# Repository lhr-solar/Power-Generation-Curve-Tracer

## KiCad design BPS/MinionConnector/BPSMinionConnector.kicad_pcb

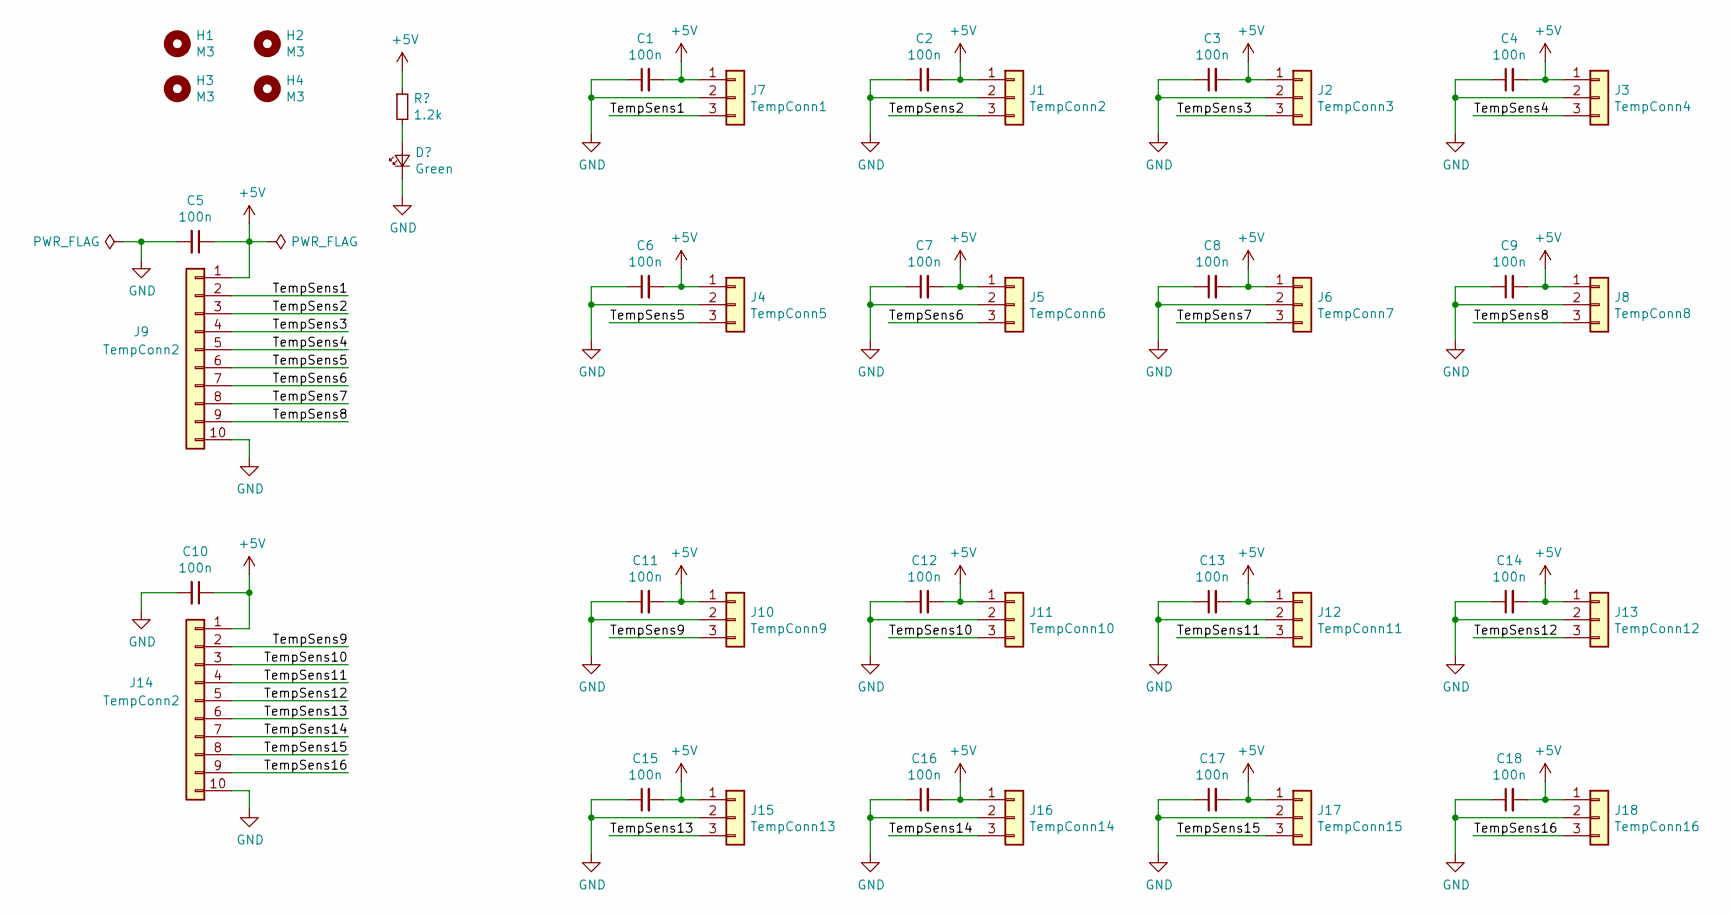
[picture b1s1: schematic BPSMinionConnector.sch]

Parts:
C1, C2, C3, C4, C5, C6, C7, C8, C9, C10, C11, C12, C13, C14, C15, C16, C17, C18: 100n; C_0805_2012Metric
H1, H2, H3, H4: M3; MountingHole_3mm
J1: TempConn2; Molex_Micro-Fit_3.0_43650-0315_1x03_P3.00mm_Vertical
J2: TempConn3; Molex_Micro-Fit_3.0_43650-0315_1x03_P3.00mm_Vertical
J3: TempConn4; Molex_Micro-Fit_3.0_43650-0315_1x03_P3.00mm_Vertical
J4: TempConn5; Molex_Micro-Fit_3.0_43650-0315_1x03_P3.00mm_Vertical
J5: TempConn6; Molex_Micro-Fit_3.0_43650-0315_1x03_P3.00mm_Vertical
J6: TempConn7; Molex_Micro-Fit_3.0_43650-0315_1x03_P3.00mm_Vertical
J7: TempConn1; Molex_Micro-Fit_3.0_43650-0315_1x03_P3.00mm_Vertical
J8: TempConn8; Molex_Micro-Fit_3.0_43650-0315_1x03_P3.00mm_Vertical
J9, J14: TempConn2; PinHeader_1x10_P2.54mm_Vertical
J10: TempConn9; Molex_Micro-Fit_3.0_43650-0315_1x03_P3.00mm_Vertical
J11: TempConn10; Molex_Micro-Fit_3.0_43650-0315_1x03_P3.00mm_Vertical
J12: TempConn11; Molex_Micro-Fit_3.0_43650-0315_1x03_P3.00mm_Vertical
J13: TempConn12; Molex_Micro-Fit_3.0_43650-0315_1x03_P3.00mm_Vertical
J15: TempConn13; Molex_Micro-Fit_3.0_43650-0315_1x03_P3.00mm_Vertical
J16: TempConn14; Molex_Micro-Fit_3.0_43650-0315_1x03_P3.00mm_Vertical
J17: TempConn15; Molex_Micro-Fit_3.0_43650-0315_1x03_P3.00mm_Vertical
J18: TempConn16; Molex_Micro-Fit_3.0_43650-0315_1x03_P3.00mm_Vertical

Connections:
+5V: C1.2, C2.2, C3.2, C4.2, C5.1, C6.2, C7.2, C8.2, C9.2, C10.1, C11.2, C12.2, C13.2, C14.2, C15.2, C16.2, C17.2, C18.2, J1.1, J2.1, J3.1, J4.1, J5.1, J6.1, J7.1, J8.1, J9.1, J10.1, J11.1, J12.1, J13.1, J14.1, J15.1, J16.1, J17.1, J18.1; also elsewhere on the board
/TempSens1: J7.3, J9.2
/TempSens2: J1.3, J9.3
/TempSens3: J2.3, J9.4
/TempSens4: J3.3, J9.5
/TempSens5: J4.3, J9.6
/TempSens6: J5.3, J9.7
/TempSens7: J6.3, J9.8
/TempSens8: J8.3, J9.9
/TempSens9: J10.3, J14.2
/TempSens10: J11.3, J14.3
/TempSens11: J12.3, J14.4
/TempSens12: J13.3, J14.5
/TempSens13: J14.6, J15.3
/TempSens14: J14.7, J16.3
/TempSens15: J14.8, J17.3
/TempSens16: J14.9, J18.3
GND: C1.1, C2.1, C3.1, C4.1, C5.2, C6.1, C7.1, C8.1, C9.1, C10.2, C11.1, C12.1, C13.1, C14.1, C15.1, C16.1, C17.1, C18.1, J1.2, J2.2, J3.2, J4.2, J5.2, J6.2, J7.2, J8.2, J9.10, J10.2, J11.2, J12.2, J13.2, J14.10, J15.2, J16.2, J17.2, J18.2; also elsewhere on the board

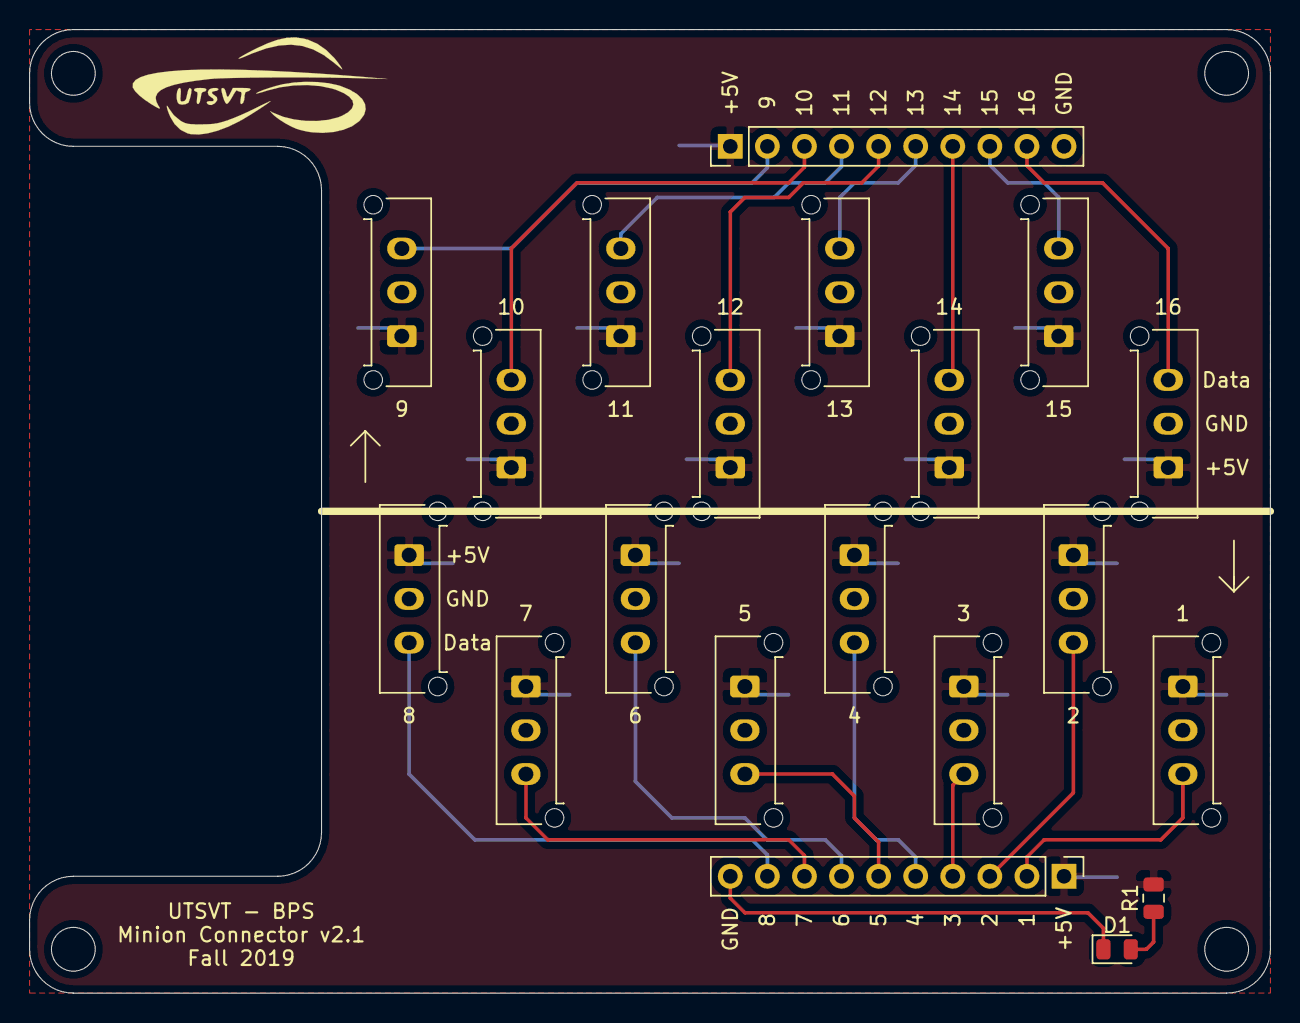
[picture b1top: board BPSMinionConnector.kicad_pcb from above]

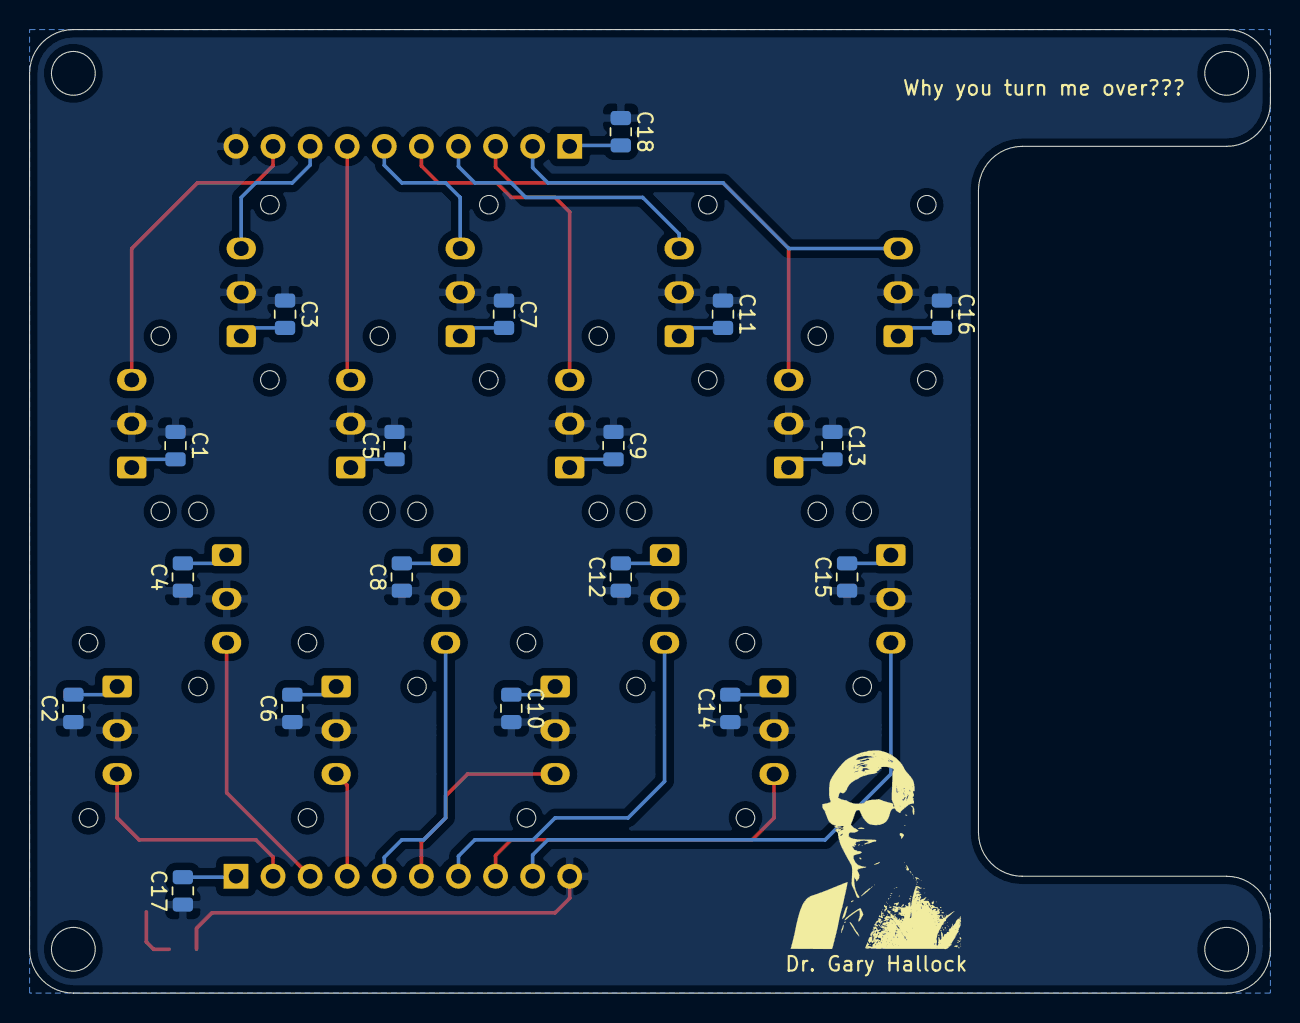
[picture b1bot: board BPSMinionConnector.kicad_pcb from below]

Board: 2 copper layers, 85.0 x 66.0 mm, 42 parts (18 on the bottom side), 19 nets.

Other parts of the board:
D1: Green; LED_0805_2012Metric
R1: 1.2k; R_0805_2012Metric

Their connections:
+5V: R1.1; also elsewhere on the board
GND: D1.1; also elsewhere on the board
unnamed: D1.2, R1.2

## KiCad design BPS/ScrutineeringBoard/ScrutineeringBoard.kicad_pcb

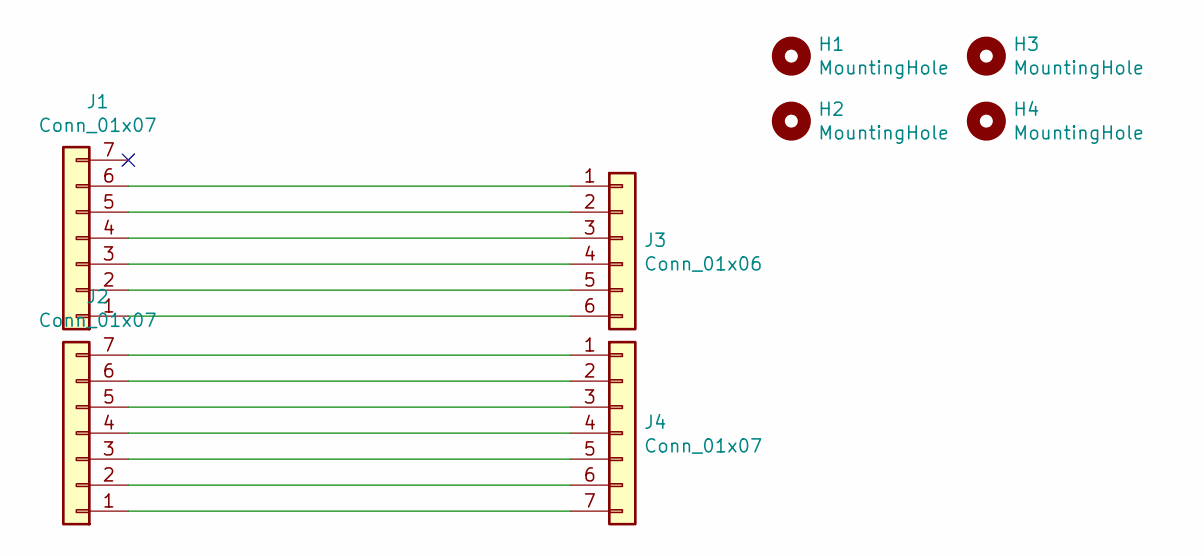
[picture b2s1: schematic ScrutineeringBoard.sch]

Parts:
H1, H2, H3, H4: MountingHole; MountingHole_3mm
J1, J2: Conn_01x07; Molex_Micro-Fit_3.0_43650-0700_1x07_P3.00mm_Horizontal
J3: Conn_01x06; PinHeader_1x06_P2.54mm_Horizontal
J4: Conn_01x07; PinHeader_1x07_P2.54mm_Horizontal

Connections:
unnamed: J1.1, J3.6
unnamed: J1.2, J3.5
unnamed: J1.3, J3.4
unnamed: J1.4, J3.3
unnamed: J1.5, J3.2
unnamed: J1.6, J3.1
unnamed: J2.1, J4.7
unnamed: J2.2, J4.6
unnamed: J2.3, J4.5
unnamed: J2.4, J4.4
unnamed: J2.5, J4.3
unnamed: J2.6, J4.2
unnamed: J2.7, J4.1

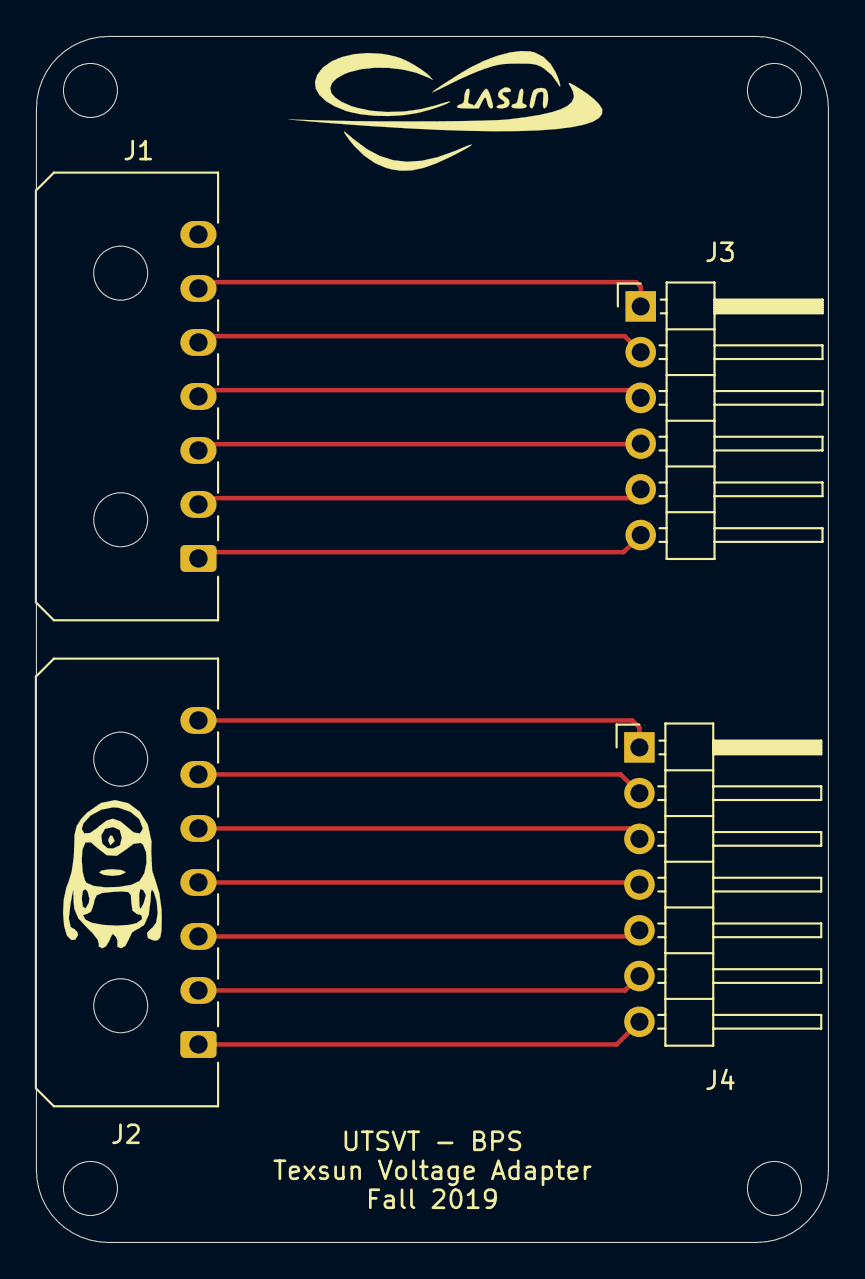
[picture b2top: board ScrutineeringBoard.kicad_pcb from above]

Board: 2 copper layers, 44.0 x 67.0 mm, 8 parts (0 on the bottom side), 13 nets.

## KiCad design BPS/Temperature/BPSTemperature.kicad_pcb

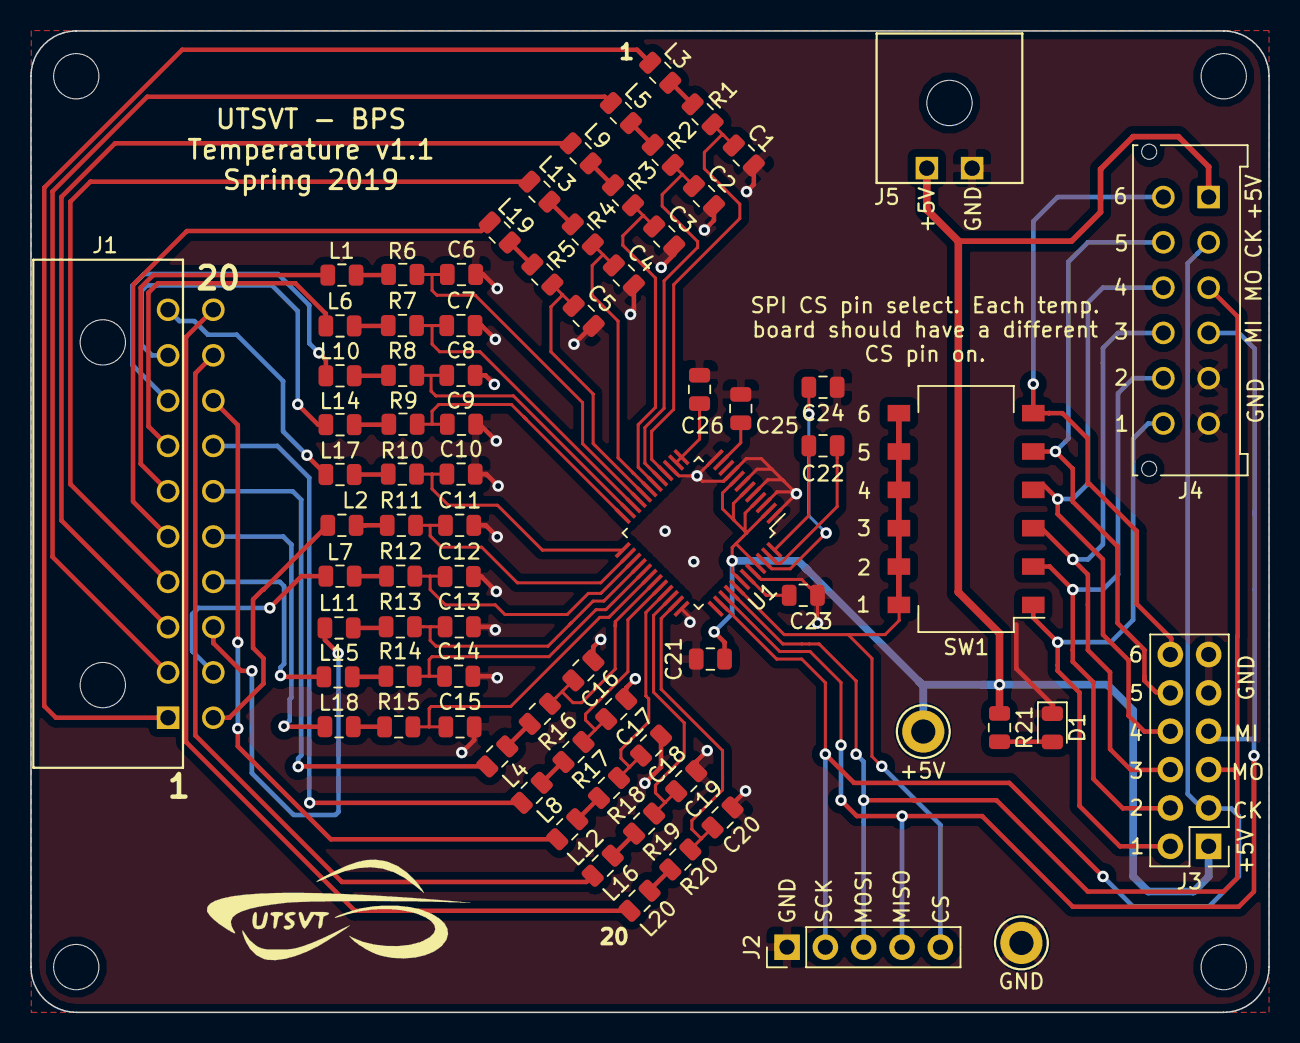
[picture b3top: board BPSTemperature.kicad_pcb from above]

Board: 2 copper layers, 82.0 x 65.0 mm, 81 parts (0 on the bottom side), 79 nets.

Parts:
C1, C2, C3, C4, C5, C6, C7, C8, C9, C10, C11, C12, C13, C14, C15, C16, C17, C18, C19, C20, C21: 0.1uF; C_0805_2012Metric
C22, C23, C24: 10uF; C_0805_2012Metric
C25, C26: 1uF; C_0805_2012Metric
D1: LED; LED_0805_2012Metric
J1: Conn_02x10_Counter_Clockwise; 02x10_Microfit_3.0_horizontal
J2: Logic Analyzer; PinHeader_1x05_P2.54mm_Vertical
J3: Conn_02x06_Counter_Clockwise; PinHeader_2x06_P2.54mm_Vertical
J4: Conn_02x06_Counter_Clockwise; Molex_MicroFit3.0_2x6xP3.00mm_PolarizingPeg_Vertical
J5: Conn_01x02; 43650-0202_01x02_Microfit 3.0_horizontal
L1, L2, L3, L4, L5, L6, L7, L8, L9, L10, L11, L12, L13, L14, L15, L16, L17, L18, L19, L20: Ferrite_Bead; L_0805_2012Metric
MH1, MH2, MH3, MH4: MountingHole; MountingHole_3mm
R1, R2, R3, R4, R5, R6, R7, R8, R9, R10, R11, R12, R13, R14, R15, R16, R17, R18, R19, R20: 1.5k; R_0805_2012Metric
R21: 1.55k; R_0805_2012Metric
SW1: SW_DIP_x06; SW_DIP_SPSTx06_Slide_Omron_A6S-610x_W8.9mm_P2.54mm
TP1, TP2: TestPoint; TestPoint_Keystone_5005-5009_Compact
U1: LTC2983; LQFP-48_7x7mm_P0.5mm

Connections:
+5V: C21.2, J3.1, J4.1, J5.1, R21.1, TP1.1, U1.2, U1.4, U1.6, U1.8, U1.42, U1.45
/CH1_LPF: J1.1, L3.2
/CH2_LPF: J1.2, L5.2
/CH3_LPF: J1.3, L9.2
/CH4_LPF: J1.4, L13.2
/CH5_LPF: J1.5, L19.2
/CH6_LPF: J1.6, L1.1
/CH7_LPF: J1.7, L6.1
/CH8_LPF: J1.8, L10.1
/CH9_LPF: J1.9, L14.1
/CH10_LPF: J1.10, L17.2
/CH11_LPF: J1.11, L2.1
/CH12_LPF: J1.12, L7.1
/CH13_LPF: J1.13, L11.1
/CH14_LPF: J1.14, L15.1
/CH15_LPF: J1.15, L18.1
/CH16_LPF: J1.16, L4.1
/CH17_LPF: J1.17, L8.1
/CH18_LPF: J1.18, L12.1
/CH19_LPF: J1.19, L16.1
/CH20_LPF: J1.20, L20.1
/CS1: J3.2, J4.12, SW1.1
/CS1_OUT: J2.5, SW1.7, SW1.8, SW1.9, SW1.10, SW1.11, SW1.12, U1.41
/CS2: J3.4, J4.11, SW1.2
/CS3: J3.6, J4.10, SW1.3
/CS4: J3.8, J4.9, SW1.4
/CS5: J3.10, J4.8, SW1.5
/CS6: J3.12, J4.7, SW1.6
/MISO: J2.4, J3.7, J4.4, U1.39
/MOSI: J2.3, J3.5, J4.3, U1.40
/SCK: J2.2, J3.3, J4.2, U1.38
GND: C1.2, C2.2, C3.2, C4.2, C5.2, C6.2, C7.2, C8.2, C9.2, C10.2, C11.2, C12.2, C13.2, C14.2, C15.2, C16.2, C17.2, C18.2, C19.2, C20.2, C21.1, C23.2, C24.2, C25.2, C26.2, D1.1, J2.1, J3.9, J3.11, J4.5, J4.6, J5.2, TP2.1, U1.1, U1.3, U1.5, U1.7, U1.9, U1.12, U1.15, U1.36, U1.44
unnamed: C1.1, R1.2, U1.16
unnamed: C2.1, R2.2, U1.17
unnamed: C3.1, R3.2, U1.18
unnamed: C4.1, R4.2, U1.19
unnamed: C5.1, R5.2, U1.20
unnamed: C6.1, R6.2, U1.21
unnamed: C7.1, R7.2, U1.22
unnamed: C8.1, R8.2, U1.23
unnamed: C9.1, R9.2, U1.24
unnamed: C10.1, R10.2, U1.25
unnamed: C11.1, R11.2, U1.26
unnamed: C12.1, R12.2, U1.27
unnamed: C13.1, R13.2, U1.28
unnamed: C14.1, R14.2, U1.29
unnamed: C15.1, R15.2, U1.30
unnamed: C16.1, R16.2, U1.31
unnamed: C17.1, R17.2, U1.32
unnamed: C18.1, R18.2, U1.33
unnamed: C19.1, R19.2, U1.34
unnamed: C20.1, R20.2, U1.35
unnamed: C22.1, U1.48
unnamed: C22.2, U1.47
unnamed: C23.1, U1.43
unnamed: C24.1, U1.46
unnamed: C25.1, U1.11
unnamed: C26.1, U1.13, U1.14
unnamed: D1.2, R21.2
unnamed: L1.2, R6.1
unnamed: L2.2, R11.1
unnamed: L3.1, R1.1
unnamed: L4.2, R16.1
unnamed: L5.1, R2.1
unnamed: L6.2, R7.1
unnamed: L7.2, R12.1
unnamed: L8.2, R17.1
unnamed: L9.1, R3.1
unnamed: L10.2, R8.1
unnamed: L11.2, R13.1
unnamed: L12.2, R18.1
unnamed: L13.1, R4.1
unnamed: L14.2, R9.1
unnamed: L15.2, R14.1
unnamed: L16.2, R19.1
unnamed: L17.1, R10.1
unnamed: L18.2, R15.1
unnamed: L19.1, R5.1
unnamed: L20.2, R20.1

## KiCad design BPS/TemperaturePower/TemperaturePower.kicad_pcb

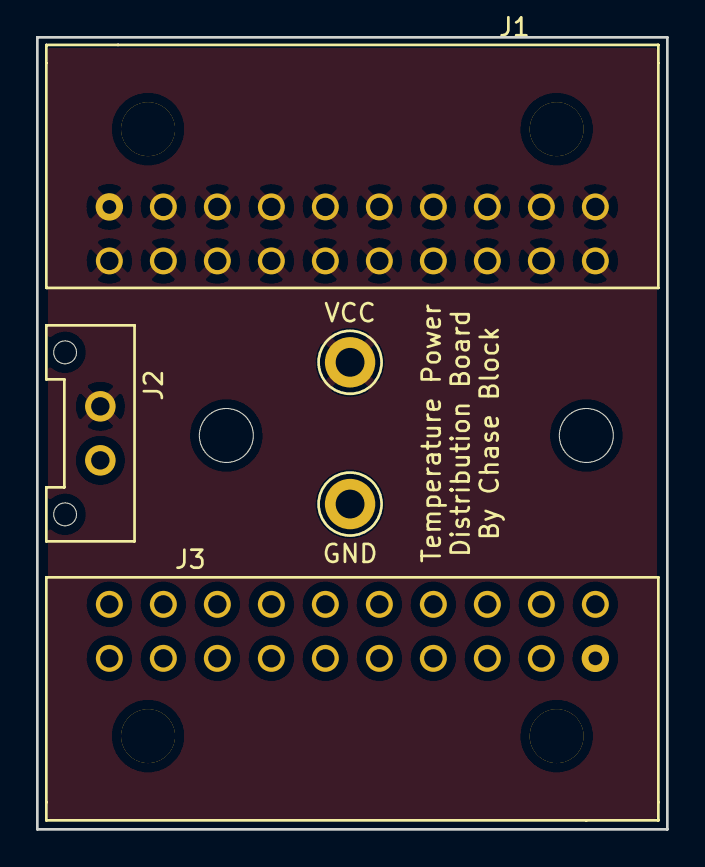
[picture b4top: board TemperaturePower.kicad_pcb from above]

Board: 2 copper layers, 35.0 x 44.0 mm, 7 parts (0 on the bottom side), 2 nets, no tracks yet.

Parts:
GND: TestPoint; TestPoint_Keystone_5005-5009_Compact
J1, J3: Conn_02x10_Counter_Clockwise; Molex2x10_horizontal
J2: Conn_01x02; Molex_MicroFit3.0_1x2xP3.00mm_PolarizingPeg_Vertical
MH1, MH2: MountingHole; MountingHole_3mm
VCC: TestPoint; TestPoint_Keystone_5005-5009_Compact

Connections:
GND: GND.1, J2.1, J3.1, J3.2, J3.3, J3.4, J3.5, J3.6, J3.7, J3.8, J3.9, J3.10, J3.11, J3.12, J3.13, J3.14, J3.15, J3.16, J3.17, J3.18, J3.19, J3.20
VCC: J1.1, J1.2, J1.3, J1.4, J1.5, J1.6, J1.7, J1.8, J1.9, J1.10, J1.11, J1.12, J1.13, J1.14, J1.15, J1.16, J1.17, J1.18, J1.19, J1.20, J2.2, VCC.1

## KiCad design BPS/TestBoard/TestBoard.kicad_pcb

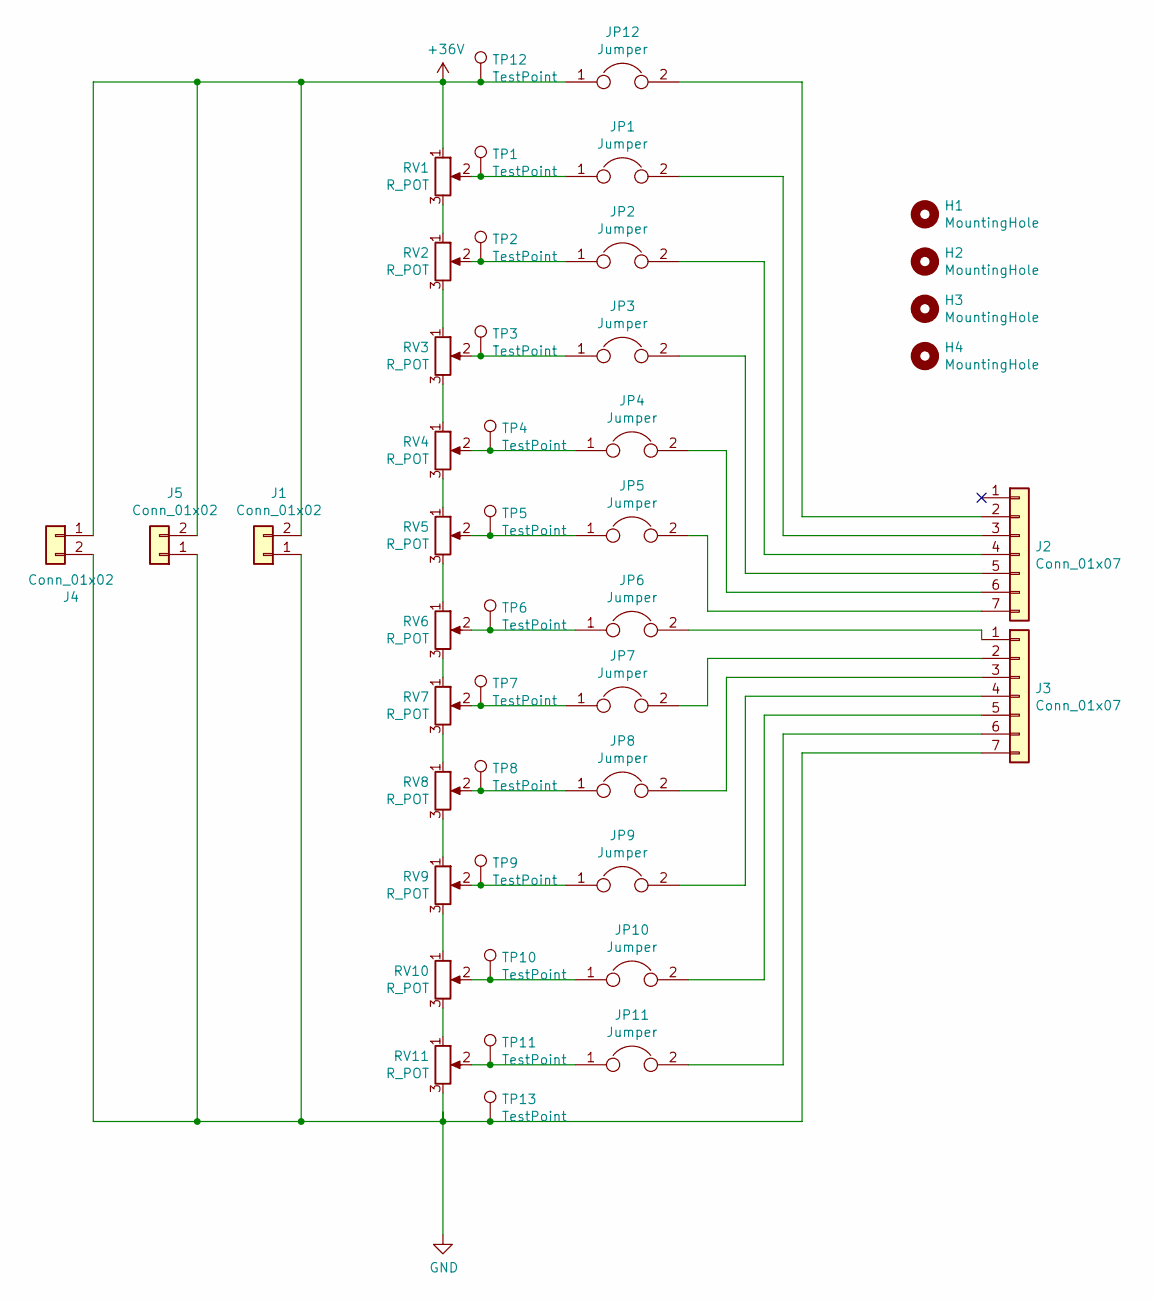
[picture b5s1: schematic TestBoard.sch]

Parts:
H1, H2, H3, H4: MountingHole; MountingHole_3mm
J1, J4, J5: Conn_01x02; PinHeader_1x02_P2.54mm_Horizontal
J2, J3: Conn_01x07; Molex_Micro-Fit_3.0_43650-0700_1x07_P3.00mm_Horizontal
JP1, JP2, JP3, JP4, JP5, JP6, JP7, JP8, JP9, JP10, JP11, JP12: Jumper; PinSocket_1x02_P2.54mm_Vertical
RV1, RV2, RV3, RV4, RV5, RV6, RV7, RV8, RV9, RV10, RV11: R_POT; Potentiometer_Piher_PT-10-V10_Vertical
TP1, TP2, TP3, TP4, TP5, TP6, TP7, TP8, TP9, TP10, TP11, TP12, TP13: TestPoint; TestPoint_Plated_Hole_D2.0mm

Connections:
+36V: J1.2, J4.1, J5.2, JP12.1, RV1.1, TP12.1
GND: J1.1, J3.7, J4.2, J5.1, RV11.3, TP13.1
unnamed: J2.2, JP12.2
unnamed: J2.3, JP1.2
unnamed: J2.4, JP2.2
unnamed: J2.5, JP3.2
unnamed: J2.6, JP4.2
unnamed: J2.7, JP5.2
unnamed: J3.1, JP6.2
unnamed: J3.2, JP7.2
unnamed: J3.3, JP8.2
unnamed: J3.4, JP9.2
unnamed: J3.5, JP10.2
unnamed: J3.6, JP11.2
unnamed: JP1.1, RV1.2, TP1.1
unnamed: JP2.1, RV2.2, TP2.1
unnamed: JP3.1, RV3.2, TP3.1
unnamed: JP4.1, RV4.2, TP4.1
unnamed: JP5.1, RV5.2, TP5.1
unnamed: JP6.1, RV6.2, TP6.1
unnamed: JP7.1, RV7.2, TP7.1
unnamed: JP8.1, RV8.2, TP8.1
unnamed: JP9.1, RV9.2, TP9.1
unnamed: JP10.1, RV10.2, TP10.1
unnamed: JP11.1, RV11.2, TP11.1
unnamed: RV1.3, RV2.1
unnamed: RV2.3, RV3.1
unnamed: RV3.3, RV4.1
unnamed: RV4.3, RV5.1
unnamed: RV5.3, RV6.1
unnamed: RV6.3, RV7.1
unnamed: RV7.3, RV8.1
unnamed: RV8.3, RV9.1
unnamed: RV9.3, RV10.1
unnamed: RV10.3, RV11.1

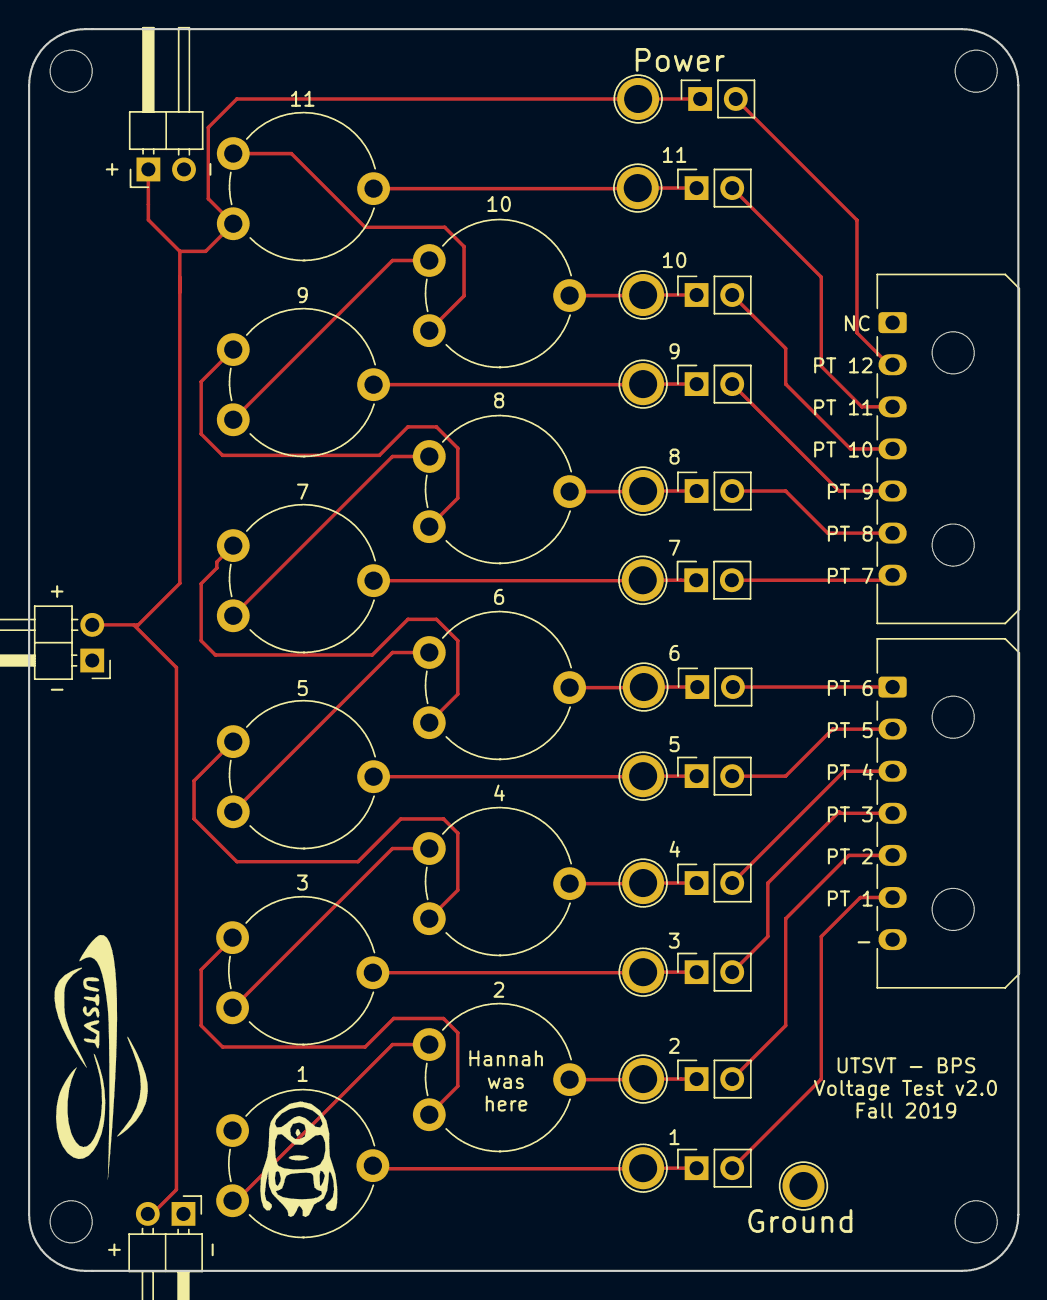
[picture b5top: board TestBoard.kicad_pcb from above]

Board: 2 copper layers, 70.5 x 88.5 mm, 45 parts (0 on the bottom side), 35 nets.

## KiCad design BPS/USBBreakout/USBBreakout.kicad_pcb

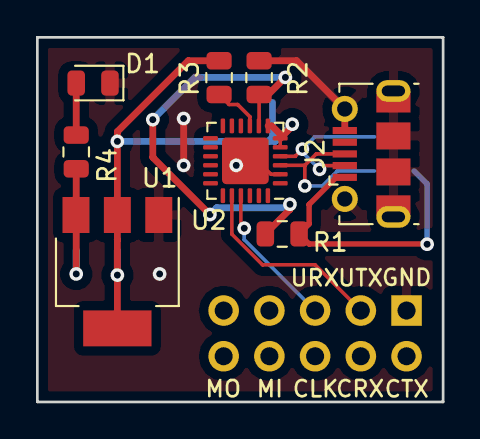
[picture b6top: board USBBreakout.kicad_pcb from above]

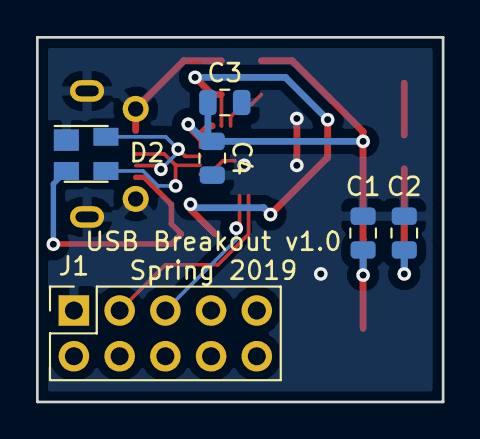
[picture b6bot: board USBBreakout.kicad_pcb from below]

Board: 2 copper layers, 22.5 x 20.3 mm, 14 parts (6 on the bottom side), 11 nets.

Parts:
C1: 10uF; C_0805_2012Metric
C2, C3: 0.1uF; C_0805_2012Metric
C4: 4.7uF; C_0805_2012Metric
D1: LED; LED_0805_2012Metric
D2: SP0503BAHT; SOT-143
J1: Conn_02x05_Odd_Even; PinSocket_2x05_P2.54mm_Vertical
J2: USB_B_Micro; USB_Micro-B_Molex-105017-0001
R1: 22.1k; R_0805_2012Metric
R2: 1k; R_0805_2012Metric
R3: 47.5k; R_0805_2012Metric
R4: 1.5k; R_0805_2012Metric
U1: NCP1117-3.3_SOT223; SOT-223-3_TabPin2
U2: CP2102N-A01-GQFN24; QFN-24-1EP_4x4mm_P0.5mm_EP2.6x2.6mm

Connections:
+3V3: C1.1, C3.1, C4.1, R2.1, U1.2, U2.5, U2.6, U2.7
+5V: C2.1, R4.1, U1.3
/D+: D2.3, J2.3, U2.3
/D-: D2.4, J2.2, U2.4
/UART1_RX: J1.5, U2.21
/UART1_TX: J1.3, U2.20
/VBUS: D2.2, J2.1, R1.2
GND: C1.2, C2.2, C3.2, C4.2, D1.1, D2.1, J1.1, J2.5, J2.6, R3.2, U1.1, U2.2, U2.25
unnamed: D1.2, R4.2
unnamed: R1.1, R3.1, U2.8
unnamed: R2.2, U2.9

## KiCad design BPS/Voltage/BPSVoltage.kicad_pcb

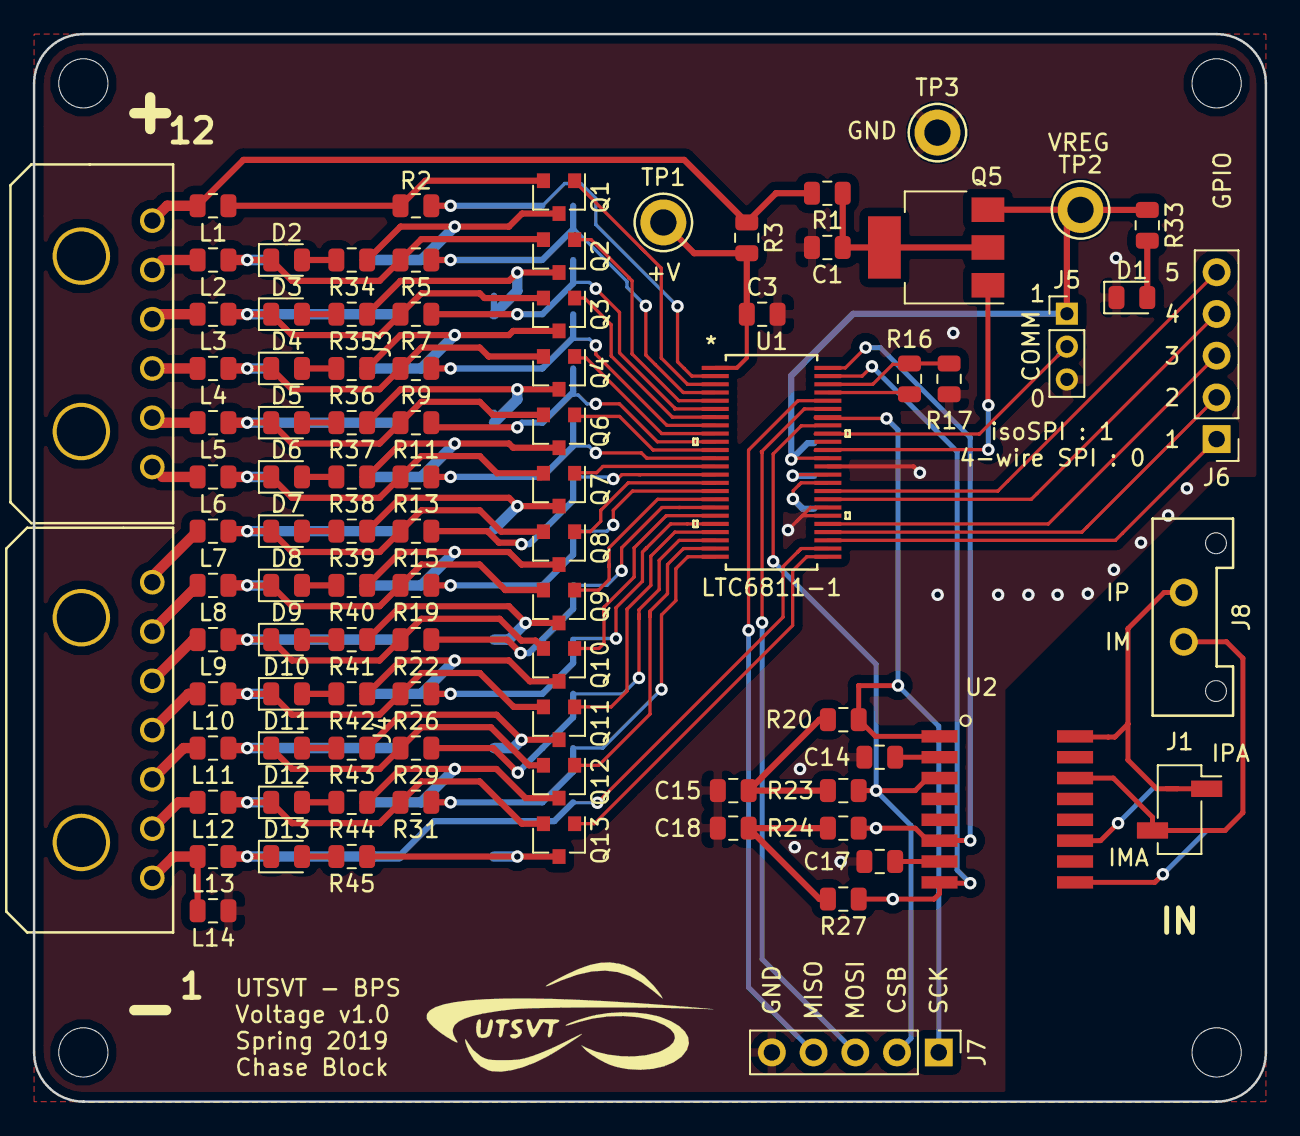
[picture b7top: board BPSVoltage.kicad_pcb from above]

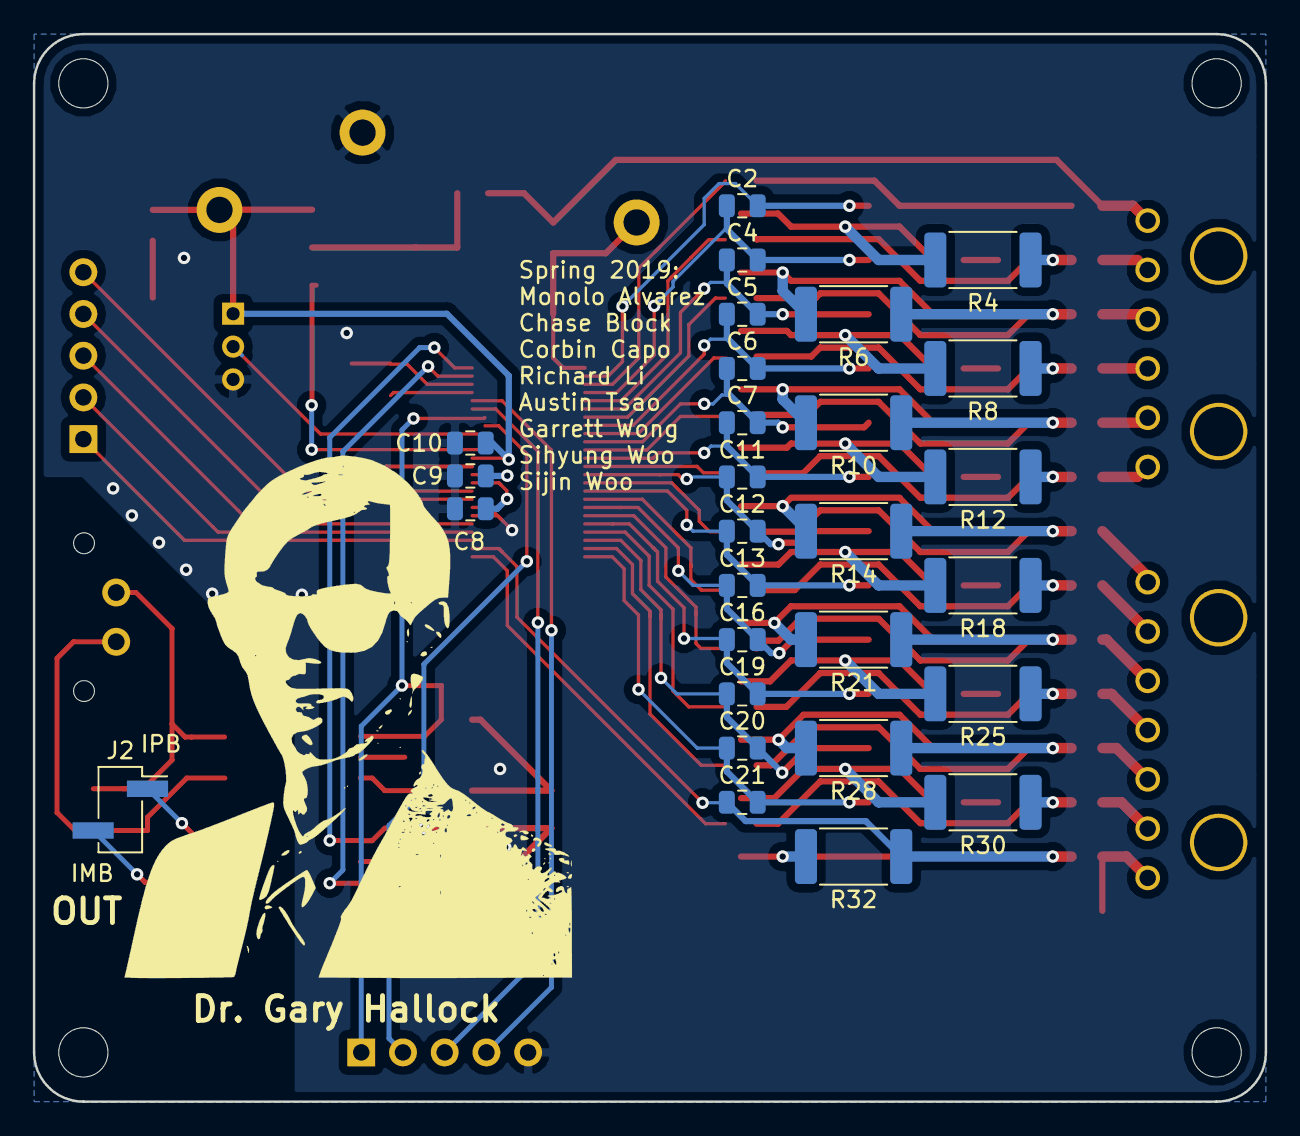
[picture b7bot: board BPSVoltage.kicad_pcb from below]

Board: 2 copper layers, 75.0 x 65.0 mm, 123 parts (28 on the bottom side), 104 nets.

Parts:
C1, C3: 100nF; C_0805_2012Metric
C2, C4, C5, C6, C7, C11, C12, C13, C14, C15, C16, C17, C18, C19, C20, C21: 10nF; C_0805_2012Metric
C8, C9, C10: 10u; C_0805_2012Metric
D1, D2, D3, D4, D5, D6, D7, D8, D9, D10, D11, D12, D13: LED; LED_0805_2012Metric
J1: Conn1; PinSocket_1x02_P2.54mm_Vertical_SMD_Pin1Right
J2: Conn2; PinHeader_1x02_P2.54mm_Vertical_SMD_Pin1Right
J3: Conn_01x06; Molex_MicroFit_01x06_Horizontal
J4: Conn_01x07; Molex_MicroFit_01x07_Horizontal
J5: Conn_01x03; PinHeader_1x03_P2.00mm_Vertical
J6, J7: Conn_01x05; PinHeader_1x05_P2.54mm_Vertical
J8: Conn_01x02; Molex_MicroFit3.0_1x2xP3.00mm_PolarizingPeg_Vertical
L1, L2, L3, L4, L5, L6, L7, L8, L9, L10, L11, L12, L13, L14: Ferrite_Bead; L_0805_2012Metric
MH1, MH2, MH3, MH4: MountingHole; MountingHole_3mm
Q1, Q2, Q3, Q4, Q6, Q7, Q8, Q9, Q10, Q11, Q12, Q13: BSS308PE; SOT-23
Q5: NSV1C201MZ4; SOT-223
R1, R2, R3, R5, R7, R9, R11, R13, R15, R19, R22, R26, R29, R31: 100R; R_0805_2012Metric
R4, R6, R8, R10, R12, R14, R18, R21, R25, R28, R30, R32: 33R; R_2512_6332Metric
R16: 806; R_0805_2012Metric
R17: 1.21k; R_0805_2012Metric
R20, R23, R24, R27: 49R9; R_0805_2012Metric
R33: 1.5k; R_0805_2012Metric
R34, R35, R36, R37, R38, R39, R40, R41, R42, R43, R44, R45: 1.2k; R_0805_2012Metric
TP1: V+; TestPoint_Keystone_5005-5009_Compact
TP2: VREG; TestPoint_Keystone_5005-5009_Compact
TP3: GND; TestPoint_Keystone_5005-5009_Compact
U1: LTC6811-1; LTC6811HG-1-PBF
U2: HX1188FNL; HXXXX

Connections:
/Batt0: C21.1, D13.1, L13.1, R32.1, U1.26
/Batt1: D12.1, L12.1, Q13.2, R30.1, R31.2
/Batt2: D11.1, L11.1, Q12.2, R28.1, R29.2
/Batt3: D10.1, L10.1, Q11.2, R25.1, R26.2
/Batt4: D9.1, L9.1, Q10.2, R21.1, R22.2
/Batt5: D8.1, L8.1, Q9.2, R18.1, R19.2
/Batt6: D7.1, L7.1, Q8.2, R14.1, R15.2
/Batt7: D6.1, L6.1, Q7.2, R12.1, R13.2
/Batt8: D5.1, L5.1, Q6.2, R10.1, R11.2
/Batt9: D4.1, L4.1, Q4.2, R8.1, R9.2
/Batt10: D3.1, L3.1, Q3.2, R6.1, R7.2
/Batt11: D2.1, L2.1, Q2.2, R4.1, R5.2
/Batt12: L1.1, Q1.2, R2.2
/GPIO1: J6.1, U1.27
/GPIO2: J6.2, U1.28
/GPIO3: J6.3, U1.29
/GPIO4: J6.4, U1.32
/GPIO5: J6.5, U1.33
/IMA: J7.2, R23.1, U1.41, U2.3
/IMB: R27.1, U1.47, U2.8
/IPA: J7.1, R20.1, U1.42, U2.1
/IPB: R24.1, U1.48, U2.6
/ISOMD: J5.2, U1.40
/L0: Q13.3, R32.2, R45.1
/L1: Q12.3, R30.2, R44.1
/L2: Q11.3, R28.2, R43.1
/L3: Q10.3, R25.2, R42.1
/L4: Q9.3, R21.2, R41.1
/L5: Q8.3, R18.2, R40.1
/L6: Q7.3, R14.2, R39.1
/L7: Q6.3, R12.2, R38.1
/L8: Q4.3, R10.2, R37.1
/L9: Q3.3, R8.2, R36.1
/L10: Q2.3, R6.2, R35.1
/L11: Q1.3, R4.2, R34.1
/SDI: J7.3, U1.43
/SDO: J7.4, U1.44
/V12: J3.6, L1.2, R1.2, R3.1
/VREG: C10.1, J5.1, Q5.3, R33.1, TP2.1, U1.37
GND: C1.2, C3.2, C8.2, C9.2, C10.2, C14.2, C15.2, C17.2, C18.2, D1.1, J5.3, J7.5, L14.1, R17.1, TP3.1, U1.30, U1.31, U1.36
unnamed: C1.1, Q5.2, Q5.4, R1.1
unnamed: C2.1, C4.2, R5.1, U1.4
unnamed: C2.2, R2.1, U1.2
unnamed: C3.1, R3.2, TP1.1, U1.1
unnamed: C4.1, C5.2, R7.1, U1.6
unnamed: C5.1, C6.2, R9.1, U1.8
unnamed: C6.1, C7.2, R11.1, U1.10
unnamed: C8.1, U1.34
unnamed: C9.1, U1.35
unnamed: C11.1, C12.2, R15.1, U1.14
unnamed: C7.1, C11.2, R13.1, U1.12
unnamed: C12.1, C13.2, R19.1, U1.16
unnamed: C13.1, C16.2, R22.1, U1.18
unnamed: C14.1, U2.2
unnamed: C15.1, R20.2, R23.2
unnamed: C16.1, C19.2, R26.1, U1.20
unnamed: C17.1, U2.7
unnamed: C18.1, R24.2, R27.2
unnamed: C19.1, C20.2, R29.1, U1.22
unnamed: C20.1, C21.2, R31.1, U1.24
unnamed: D1.2, R33.2
unnamed: D2.2, R34.2
unnamed: D3.2, R35.2
unnamed: D4.2, R36.2
unnamed: D5.2, R37.2
unnamed: D6.2, R38.2
unnamed: D7.2, R39.2
unnamed: D8.2, R40.2
unnamed: D9.2, R41.2
unnamed: D10.2, R42.2
unnamed: D11.2, R43.2
unnamed: D12.2, R44.2
unnamed: D13.2, R45.2
unnamed: J1.1, J8.1, U2.16
unnamed: J1.2, J8.2, U2.14
unnamed: J2.1, U2.11
unnamed: J2.2, U2.9
unnamed: J3.1, L6.2
unnamed: J3.2, L5.2
unnamed: J3.3, L4.2
unnamed: J3.4, L3.2
unnamed: J3.5, L2.2
unnamed: J4.1, L13.2, L14.2
unnamed: J4.2, L12.2
unnamed: J4.3, L11.2
unnamed: J4.4, L10.2
unnamed: J4.5, L9.2
unnamed: J4.6, L8.2
unnamed: J4.7, L7.2
unnamed: Q1.1, U1.3
unnamed: Q2.1, U1.5
unnamed: Q3.1, U1.7
unnamed: Q4.1, U1.9
unnamed: Q5.1, U1.38
unnamed: Q6.1, U1.11
unnamed: Q7.1, U1.13
unnamed: Q8.1, U1.15
unnamed: Q9.1, U1.17
unnamed: Q10.1, U1.19
unnamed: Q11.1, U1.21
unnamed: Q12.1, U1.23
unnamed: Q13.1, U1.25
unnamed: R16.1, R17.2, U1.46
unnamed: R16.2, U1.45

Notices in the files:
parts and their libraries:
Copyright 2016 Accelerated Designs. All rights reserved.
